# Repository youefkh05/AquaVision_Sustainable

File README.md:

# Lake Sensing Project

>[!IMPORTANT]
> This project is done as part of the Embedded Systems course [ELC2080] taught to second year Electronics and Elecrtic Communication Engineering Students at Cairo University Under the Supervision of Dr. Mohamed Riad.

### **[Dashboard Link](https://amirsameh1.github.io/test/)** To monitor project Data in real-time

## Brief Description

The system employs a dual-microcontroller setup to monitor and transmit water level data at two locations in a lake. The first module, positioned at the center where GSM signal is unavailable, measures water level and temperature, then relays the data via the ESP-NOW protocol to a second module stationed at the lake’s edge. This second unit consolidates the readings and transmits them to a base station using both GSM and Wi-Fi for broader connectivity.

## Project Features:

- Real Time Water-Level and temprature updates
- Accurate Data Measurments using different sensors
- Tracking measurements at two different locations
- Intiutive dashboard displaying data
- GSM connectivity
- Creative UI on Oled inspired by the Flipper Zero UI
- Alarm system if the Water Level is under a specified Limit

## Technical Highlights:

- Uses ESP32 Microcontroller for its wireless capability
- ESP-NOW Protocol used for communication between the two nodes
- GSM Connectivity Sends data to the dashboard in Real-Time.
- Overcoming GSM Challenges using an SMS system.
- Custom designed PCB for Each Node
    - Double Layer for Middle Node
    - Single Layer for Edge Node
- Power Supply filtering circuit to ensure safe operation of all components used
- Measuring water levels using two different methods
    - Ultrasonic Sensor
    - Time of Flight (ToF) Sensor
- Firbase used for storing and collecting data

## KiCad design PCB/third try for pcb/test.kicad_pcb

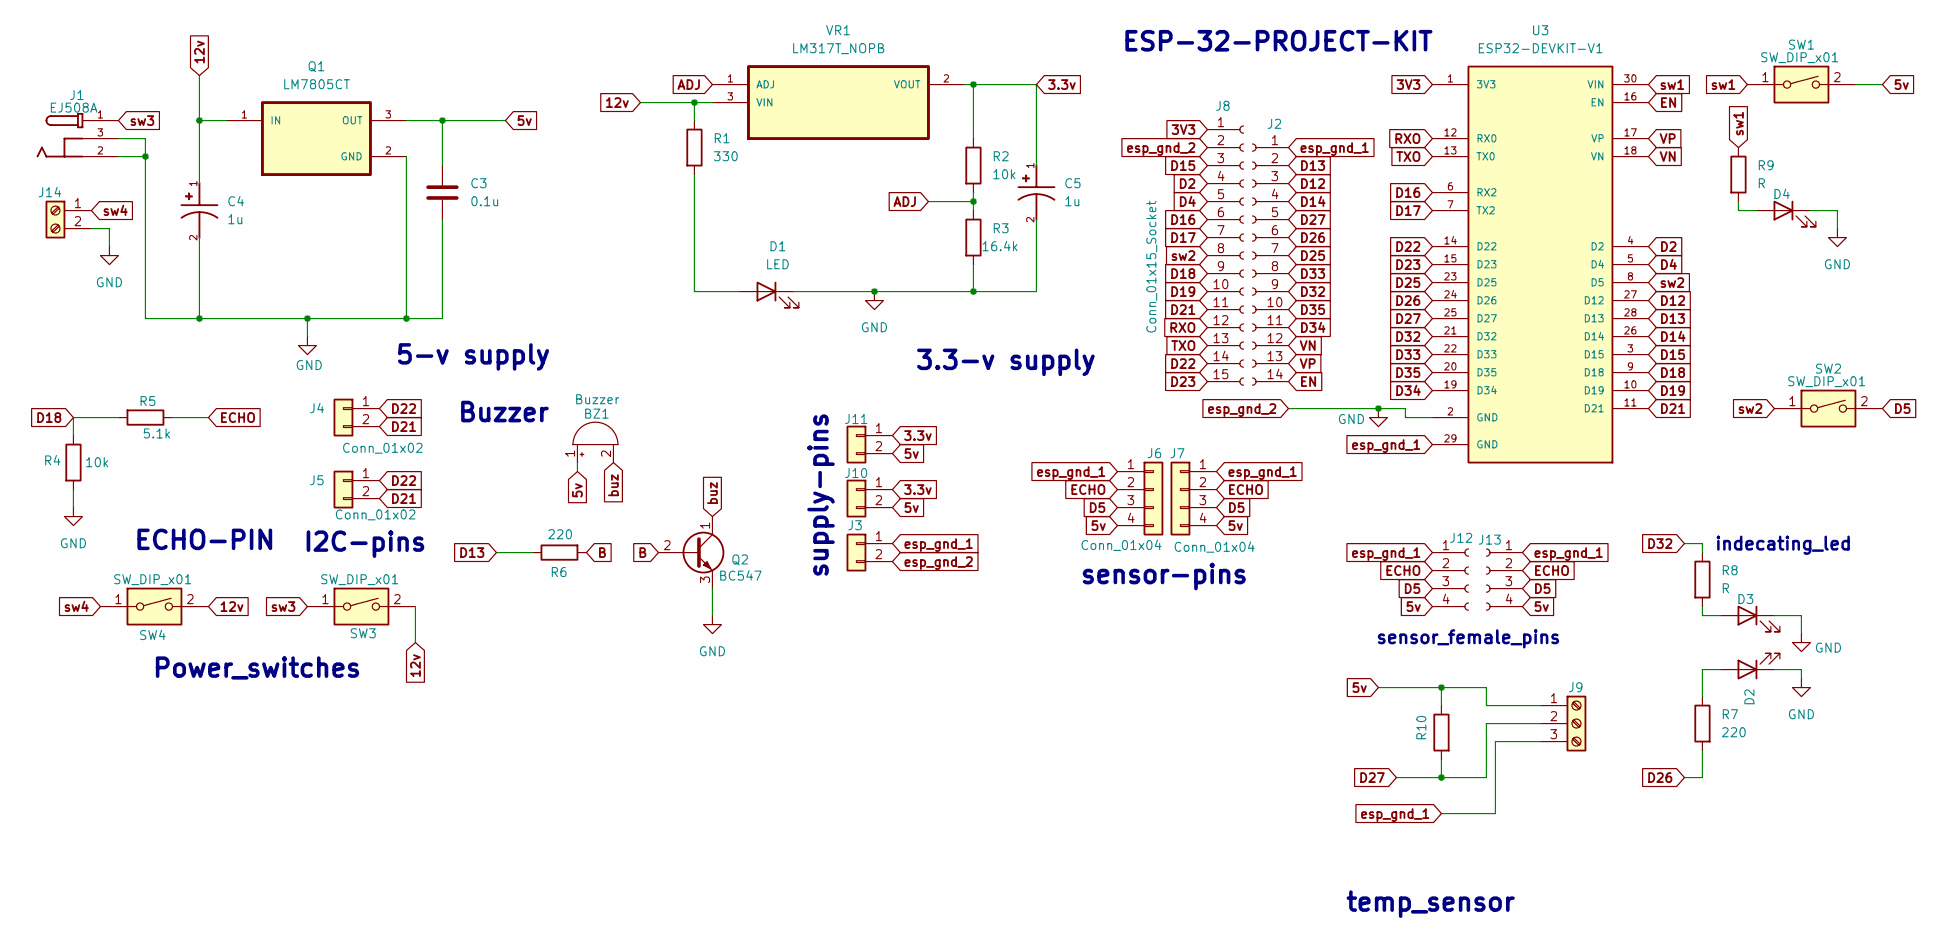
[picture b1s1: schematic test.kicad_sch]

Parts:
BZ1: Buzzer; Buzzer_12x9.5RM7.6
C3: 0.1u; C_Disc_D3.0mm_W2.0mm_P2.50mm
C4, C5: 1u; CAPPRD500W60D1330H2700; PARTREV Apr-20
D1, D2, D3, D4: LED; LED_D5.0mm
J1: EJ508A; MPD_EJ508A; PARTREV J
J2: Conn_01x14_Socket; PinSocket_1x14_P2.54mm_Vertical
J3, J4, J5, J10, J11: Conn_01x02; PinHeader_1x02_P2.54mm_Vertical
J6, J7: Conn_01x04; PinHeader_1x04_P2.54mm_Vertical
J8: Conn_01x15_Socket; PinSocket_1x15_P2.54mm_Vertical
J9: Screw_Terminal_01x03; TerminalBlock_Phoenix_MKDS-1,5-3_1x03_P5.00mm_Horizontal
J12, J13: Conn_01x04_Socket; PinSocket_1x04_P2.54mm_Vertical
J14: Screw_Terminal_01x02; TerminalBlock_Phoenix_MKDS-1,5-2_1x02_P5.00mm_Horizontal
Q1: LM7805CT; TO254P1054X470X2600-3; PARTREV LTR
Q2: BC547; TO92260P476H877-3
R1: 330; R_Axial_DIN0309_L9.0mm_D3.2mm_P15.24mm_Horizontal
R2, R4: 10k; R_Axial_DIN0309_L9.0mm_D3.2mm_P15.24mm_Horizontal
R3: 16.4k; R_Axial_DIN0309_L9.0mm_D3.2mm_P15.24mm_Horizontal
R5: 5.1k; R_Axial_DIN0309_L9.0mm_D3.2mm_P15.24mm_Horizontal
R6, R7: 220; R_Axial_DIN0309_L9.0mm_D3.2mm_P15.24mm_Horizontal
R8, R9: R; R_Axial_DIN0309_L9.0mm_D3.2mm_P15.24mm_Horizontal
R10: R_Axial_DIN0309_L9.0mm_D3.2mm_P15.24mm_Horizontal
SW1, SW2, SW3, SW4: SW_DIP_x01; SW_DIP_SPSTx01_Slide_9.78x4.72mm_W7.62mm_P2.54mm
U3: ESP32-DEVKIT-V1; MODULE_ESP32_DEVKIT_V1; PARTREV N/A
VR1: LM317T_NOPB; TO254P1054X470X1955-3

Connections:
3.3v: C5.1, J10.1, J11.1, R2.1, VR1.2 (VOUT)
3V3: J8.1, U3.1 (3V3)
5v: BZ1.1 (+), C3.1, J6.4, J7.4, J9.1, J10.2, J11.2, J12.4, J13.4, Q1.3 (OUT), R10.1, SW1.2
12v: C4.1, Q1.1 (IN), R1.1, SW3.2, SW4.2, VR1.3 (VIN)
ADJ: R2.2, R3.1, VR1.1 (ADJ)
B: Q2.2 (B), R6.2
D2: J8.4, U3.4 (D2)
D4: J8.5, U3.5 (D4)
D5: J6.3, J7.3, J12.3, J13.3, SW2.2
D12: J2.3, U3.27 (D12)
D13: J2.2, R6.1, U3.28 (D13)
D14: J2.4, U3.26 (D14)
D15: J8.3, U3.3 (D15)
D16: J8.6, U3.6 (RX2)
D17: J8.7, U3.7 (TX2)
D18: J8.9, R4.1, R5.2, U3.9 (D18)
D19: J8.10, U3.10 (D19)
D21: J4.2, J5.2, J8.11, U3.11 (D21)
D22: J4.1, J5.1, J8.14, U3.14 (D22)
D23: J8.15, U3.15 (D23)
D25: J2.7, U3.23 (D25)
D26: J2.6, R7.2, U3.24 (D26)
D27: J2.5, J9.2, R10.2, U3.25 (D27)
D32: J2.9, R8.1, U3.21 (D32)
D33: J2.8, U3.22 (D33)
D34: J2.11, U3.19 (D34)
D35: J2.10, U3.20 (D35)
ECHO: J6.2, J7.2, J12.2, J13.2, R5.1
EN: J2.14, U3.16 (EN)
unnamed: D1.2 (A), R1.2
unnamed: D2.2 (A), R7.1
unnamed: D3.2 (A), R8.2
unnamed: D4.2 (A), R9.2
RXO: J8.12, U3.12 (RX0)
TXO: J8.13, U3.13 (TX0)
VN: J2.12, U3.18 (VN)
VP: J2.13, U3.17 (VP)
buz: BZ1.2 (-), Q2.1 (C)
esp_gnd_1: J2.1, J3.1, J6.1, J7.1, J9.3, J12.1, J13.1, U3.29 (GND)
esp_gnd_2: C3.2, C4.2, C5.2, D1.1 (K), D2.1 (K), D3.1 (K), D4.1 (K), J1.2, J1.3, J3.2, J8.2, J14.2, Q1.2 (GND), Q2.3 (E), R3.2, R4.2, U3.2 (GND)
sw1: R9.1, SW1.1, U3.30 (VIN)
sw2: J8.8, SW2.1, U3.8 (D5)
sw3: J1.1, SW3.1
sw4: J14.1, SW4.1

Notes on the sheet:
supply-pins
Buzzer
ESP-32-PROJECT-KIT
ECHO-PIN
temp_sensor
3.3-v supply
sensor-pins
indecating_led
sensor_female_pins
5-v supply
Power_switches
I2C-pins

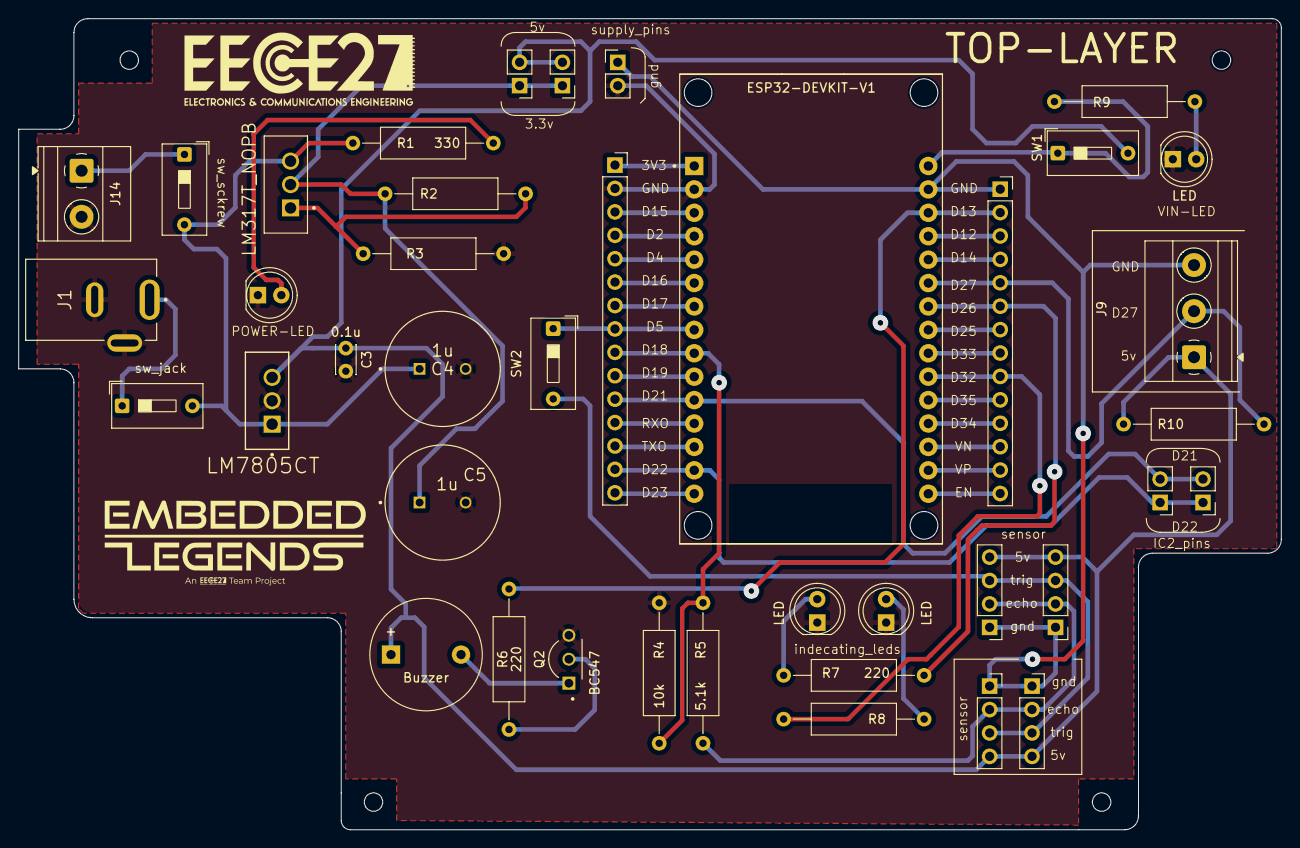
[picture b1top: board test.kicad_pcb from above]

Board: 2 copper layers, 137.0 x 88.0 mm, 40 parts (0 on the bottom side), 44 nets.

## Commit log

2025-02-26 Project First Steps
2025-02-26 Comments
2025-02-26 Change Project Name
2025-02-26 Second MCU Project and extra comments
2025-02-27 Average a5er 5amas 2erayat
2025-02-27 removed todo for average a5er 5amas 2erayat
2025-02-28 ESPNOW Sender and Receiver codes
    these are the code I have written until now for the Communication between Two esp32
2025-02-28 ESPNow Sender
2025-02-28 ESPNOW_Reciever
2025-02-28 Temp sensor
2025-03-01 adjusted pins
2025-03-01 Adjusted ESPNOW Send Sktech
2025-03-01 comments on second file
2025-03-04 oled test project
2025-03-04 small edits
2025-03-05 ESPNow fixes
2025-03-05 MCU2 compiles
2025-03-05 more edits
2025-03-05 working reciver code
2025-03-05 firebase using wifi
    this is the previous code I have worked on it before
2025-03-05 SIM800L Driver
    this is the driver of GSM for SIM800L , but still have a problem of HTTPS connection
2025-03-05 Firebase module using GSM
    this is the firebase module driver using GSM
2025-03-06 Oled final
2025-03-13 Waterproof test
2025-03-13 Temprature Sensor done
2025-03-13 firebase problems
2025-03-13 these are the updates for files for solving espnow and firebase connection problem
2025-03-14 vjfgjf
2025-03-15 Water Edge | Main Code Cleanup
2025-03-15 More Fine touches
2025-03-15 Code Clean up
2025-03-15 Tiny Edit
2025-03-15 Fixed OLED
2025-03-16 Added Push Button Debounce MCU2
2025-03-16 Changed Used sensor in MCU2 to ToF
2025-03-16 Data Reception LED Configured
2025-03-18 firebase stuff enw
2025-03-18 Firebase Ziad
2025-03-18 Firebase stuff (Failed Test)
2025-03-18 Changed Channel for ESPNOW
2025-03-18 added JSN init
2025-03-19 Current Sensor Var for MCu1
2025-03-19 Changed ESP to Channel 1
2025-03-24 Removed todo in main MCU1
2025-03-24 Adjusted serial commands and removed unnecessary delay
2025-03-24 Turn Off FIrebase Temporarily
2025-04-13 Team Graphics
2025-04-14 Oled updates
2025-04-14 firebase sender, main: changes
2025-04-14 Set Current sensor variable to tof
2025-04-14 changed sensor to HCSR04
2025-04-14 Changed MCU2 sensor to ToF
2025-04-14 Added a variable to control data measurment
2025-04-14 solve the problem of disapearing the diplayed digits of water level 2
    بارك الله فيما رزق
2025-04-15 changed network to ameer's hotspot
2025-04-17 pin changes mcu 1 pcb
2025-04-17 adding interrupt feature
2025-04-18 stuff are now working a bit
2025-04-18 turned it back to sync
2025-04-18 Problem figured out and fixed
2025-04-19 added an ESPNOW DeInit Function
2025-04-24 GSM Updates
2025-04-27 adjusted GSM sms message to sender code
2025-04-27 Edited phone number to kareem's
2025-05-08 fixed GSM format and added options for data upload
2025-06-08 Adjusted read me and added some graphics
2025-06-08 Adjusted Readme further more
2025-06-08 Added dashboard link in readme
2025-06-08 Made it bold
2025-06-15 Added Debug functions in Middle Module
2025-06-15 buzzer thing
2025-06-15 adjusted GSM uart pins
2025-06-17 added debug LED and fixed some gsm stuff
2025-06-18 Adjusted Water level to measured depth
2025-06-18 Adjusted to measure depth
2025-06-20 Readme Changes
2025-06-22 Uploaded project photos and fixed logo in readme
2025-07-23 Added finiished research
    We updated it by adding the PCB prototype
2025-07-24 Added Final presentation
    it needs the animations
2025-07-24 Finished Animation
    It looks good!
2025-07-28 Added WIFI
    now it can aceess the WIFI
2025-07-28 Edited the slides
    It needs the video
2025-07-28 Added AI chat bot
    It will use Bluetooth
2025-07-28 added AI
    it uses MatLab
2025-08-09 finished AI Prototype
    It works as an AI Prototype back end
2025-08-09 Aquavision App Initail
    Added the nessacry Initial Code
2025-08-10 front end created
    so far looks good
2025-08-10 ESP initialized
    Now we can access the ESP32
2025-08-10 Added Reading variables
    now we can read the variables from the ESP32
2025-08-10 Added AI Prototype
    It works well
2025-08-10 Added Catlog
    It resmebles our product as a start up
2025-08-10 Added URL upload
    Now our app udpoalds its data on the dashboard
2025-08-10 Integrated the Dashboard
    Now the application uploads the data on the dashbaord
2025-08-11 Added PCB
    now we can view it
2025-08-11 Made the application officially
    Now we have an executable application that runs without the MatLab
2025-09-02 Added AI model test
    it'll be integrated
2025-09-15 IEEE ESPC
    We're going to participate !
2025-09-15 Finished the cover page
    we just need to sign!
2025-09-16 added our signs
    we will submit!
2025-10-10 Created using Colab
